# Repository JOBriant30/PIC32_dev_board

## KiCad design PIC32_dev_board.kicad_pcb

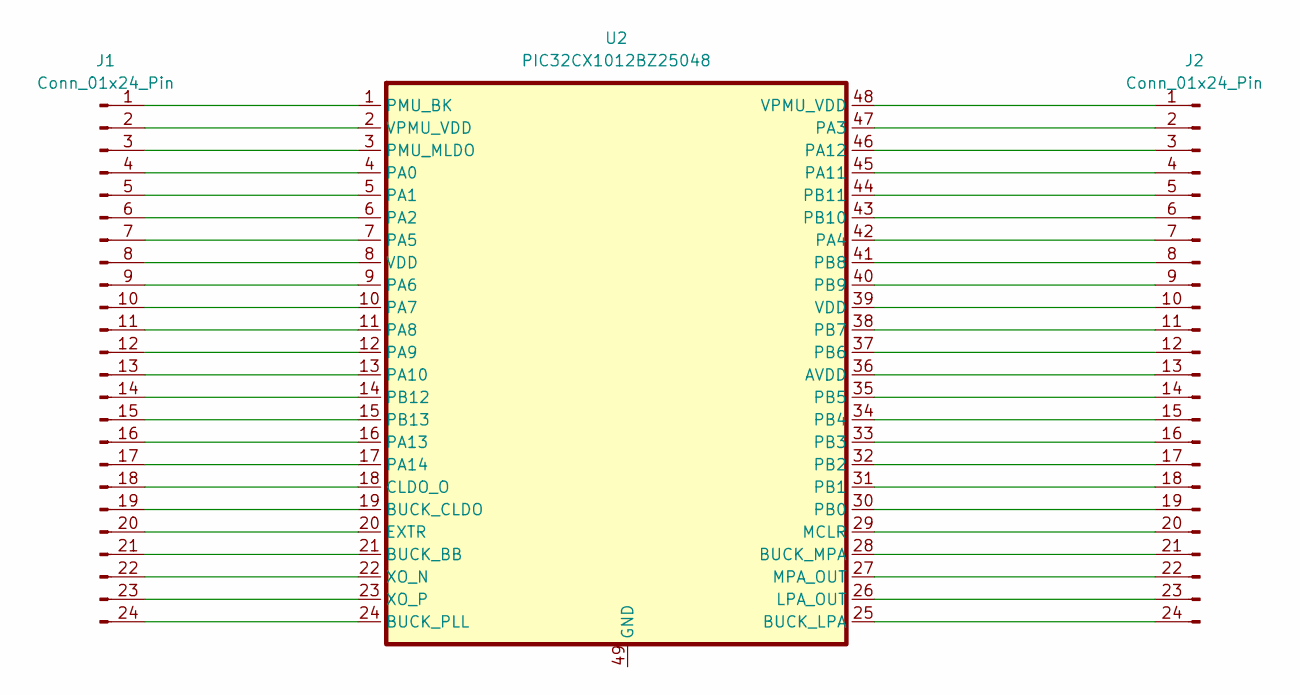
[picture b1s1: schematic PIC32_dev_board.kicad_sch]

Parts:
J1, J2: Conn_01x24_Pin; PinHeader_1x24_P1.00mm_Vertical
U2: PIC32CX1012BZ25048; VQFN-48-1EP_7x7mm_P0.5mm_EP4.1x4.1mm

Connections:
unnamed: J1.1, U2.1 (PMU_BK)
unnamed: J1.2, U2.2 (VPMU_VDD)
unnamed: J1.3, U2.3 (PMU_MLDO)
unnamed: J1.4, U2.4 (PA0)
unnamed: J1.5, U2.5 (PA1)
unnamed: J1.6, U2.6 (PA2)
unnamed: J1.7, U2.7 (PA5)
unnamed: J1.8, U2.8 (VDD)
unnamed: J1.9, U2.9 (PA6)
unnamed: J1.10, U2.10 (PA7)
unnamed: J1.11, U2.11 (PA8)
unnamed: J1.12, U2.12 (PA9)
unnamed: J1.13, U2.13 (PA10)
unnamed: J1.14, U2.14 (PB12)
unnamed: J1.15, U2.15 (PB13)
unnamed: J1.16, U2.16 (PA13)
unnamed: J1.17, U2.17 (PA14)
unnamed: J1.18, U2.18 (CLDO_O)
unnamed: J1.19, U2.19 (BUCK_CLDO)
unnamed: J1.20, U2.20 (EXTR)
unnamed: J1.21, U2.21 (BUCK_BB)
unnamed: J1.22, U2.22 (XO_N)
unnamed: J1.23, U2.23 (XO_P)
unnamed: J1.24, U2.24 (BUCK_PLL)
unnamed: J2.1, U2.48 (VPMU_VDD)
unnamed: J2.2, U2.47 (PA3)
unnamed: J2.3, U2.46 (PA12)
unnamed: J2.4, U2.45 (PA11)
unnamed: J2.5, U2.44 (PB11)
unnamed: J2.6, U2.43 (PB10)
unnamed: J2.7, U2.42 (PA4)
unnamed: J2.8, U2.41 (PB8)
unnamed: J2.9, U2.40 (PB9)
unnamed: J2.10, U2.39 (VDD)
unnamed: J2.11, U2.38 (PB7)
unnamed: J2.12, U2.37 (PB6)
unnamed: J2.13, U2.36 (AVDD)
unnamed: J2.14, U2.35 (PB5)
unnamed: J2.15, U2.34 (PB4)
unnamed: J2.16, U2.33 (PB3)
unnamed: J2.17, U2.32 (PB2)
unnamed: J2.18, U2.31 (PB1)
unnamed: J2.19, U2.30 (PB0)
unnamed: J2.20, U2.29 (MCLR)
unnamed: J2.21, U2.28 (BUCK_MPA)
unnamed: J2.22, U2.27 (MPA_OUT)
unnamed: J2.23, U2.26 (LPA_OUT)
unnamed: J2.24, U2.25 (BUCK_LPA)

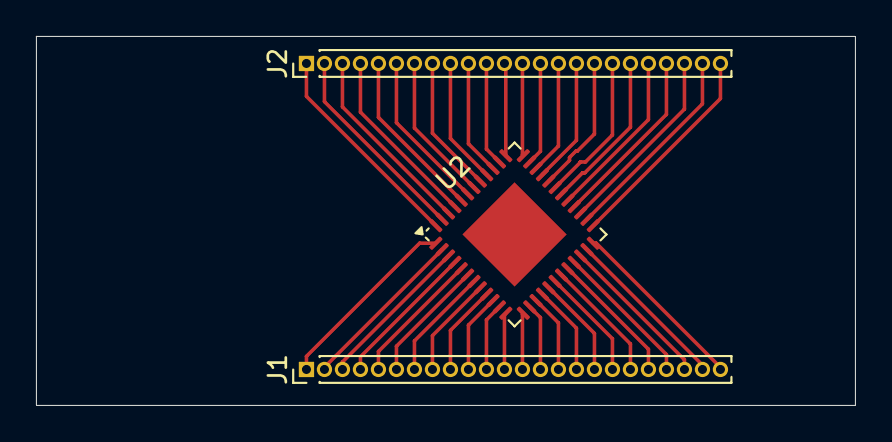
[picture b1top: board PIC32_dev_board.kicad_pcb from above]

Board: 2 copper layers, 45.5 x 20.5 mm, 3 parts (0 on the bottom side), 48 nets.

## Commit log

2025-05-16 Initial commit of KiCad project
2025-05-30 still working on routing
2025-06-06 routed breakout board
